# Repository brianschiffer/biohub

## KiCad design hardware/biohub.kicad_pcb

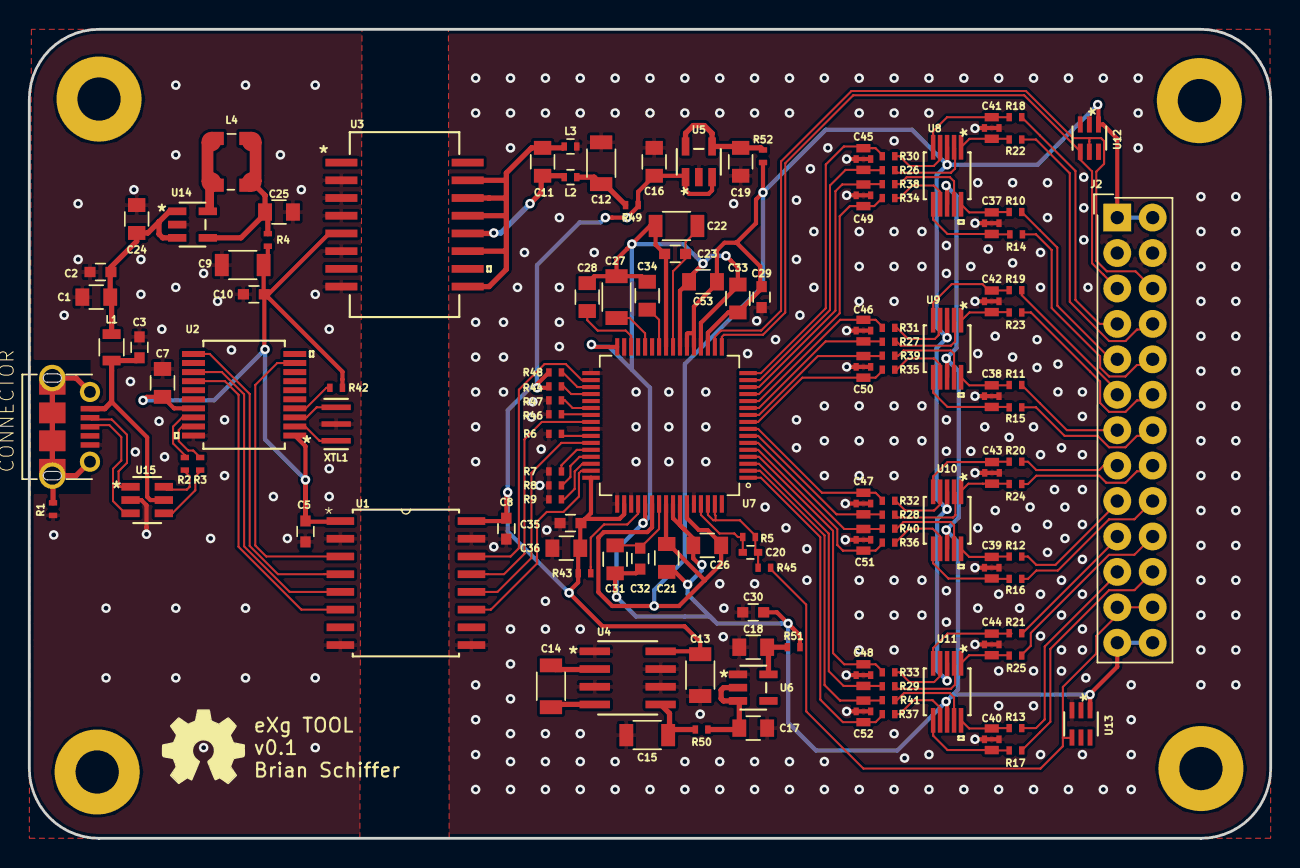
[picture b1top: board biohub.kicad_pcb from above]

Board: 4 copper layers, 89.0 x 58.0 mm, 125 parts (0 on the bottom side), 120 nets.

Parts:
C1, C24, C25: 4.7u; C_0805
C2, C5, C8, C10, C23, C29, C30, C32, C35: 0.1u; C_0603
C3: 10nF; C_0603
C7, C11: 0.22u; C_0805
C9, C12, C13, C14, C15, C22: 10u; C_1206
C16, C17, C18, C19: 2.2u; C_0805
C20: 1n; C_0402
C21, C26, C28, C31, C33, C34, C36, C53: 1u; C_0805
C27: 100u; C_1206
C37, C38, C39, C40, C41, C42, C43, C44: X2Y 10n; 500X14W103MV4T
C45, C46, C47, C48, C49, C50, C51, C52: X2Y 0.22u; 160X14X224MV4T
J1: CONNECTOR; MOLEX_1050170001
J2: Conn_02x13_Odd_Even; MOLEX_70247_2652_2x13
L1: 600R/2A; L_0805
L2, L3: 2.2R/0.2A; L_0402
L4: 4.7uH; L_Wuerth_WE-TPC
R1, R6, R7, R8, R9, R42, R43, R44, R46, R47, R48: 10k; R_0402_NoSilk
R2, R3: 27; R_0402_NoSilk
R4, R49, R50, R51, R52: 0; R_0402_NoSilk
R5, R45: 1M; R_0402_NoSilk
R10, R11, R12, R13, R14, R15, R16, R17, R18, R19, R20, R21, R22, R23, R24, R25: 4.02k 0.1%; R_0402_NoSilk
R26, R27, R28, R29, R30, R31, R32, R33, R34, R35, R36, R37, R38, R39, R40, R41: 10k 0.1%; R_0402_NoSilk
U1: ADUM1412BRWZ
U2: MCP2210-I_SS; MCP2210
U3: ADUM6020
U4: ADM8660ARZ
U5: ADP7142AUJZ-2.5-R7; ADP7142AUJZ-R7
U6: ADP7182AUJZ-2.5-R7; ADP7182AUJZ-R7
U7: ADS1299IPAG
U8, U9, U10, U11: AD8244BRMZ
U12, U13: TPD4E1B06DCKR
U14: MCP1603T-330I
U15: USBLC6-2SC6; USBLC62
XTL1: CSTNE12M0GH5L000R0

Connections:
+2V5: C21.2, C26.2, C29.2, C33.2, C53.2, J2.1, J2.2, R52.2, U7.19, U7.21, U7.22, U7.54, U7.56, U7.59, U8.3, U9.3, U10.3, U11.3, U12.1
+3V3: C8.1, C13.1, C16.1, C35.2, C36.2, R43.1, R44.1, R48.1, R49.2, U1.16, U4.8, U5.1, U5.3, U7.48, U7.50
-2V5: C21.1, C22.1, C23.1, C26.1, C27.1, C28.1, C30.1, C31.1, C32.1, C33.1, C34.1, C53.1, J2.25, J2.26, R51.2, U7.20, U7.23, U7.25, U7.32, U7.53, U7.57, U7.58, U8.8, U9.8, U10.8, U11.8, U13.1
-3V3: C17.1, R50.2, U6.2, U6.3
/AFE/BIAS: J2.23, J2.24, R45.1, U13.4
/AFE/DRDY: U1.11, U7.47
/AFE/MISO: U1.12, U7.43
/AFE/MOSI: U1.14, U7.34
/AFE/SCLK: U1.13, U7.40
/AFE/SRB1: J2.5, U7.17, U12.4
/AFE/SRB2: J2.6, U7.18, U12.5
/interface/1N: C45.1, R26.1, U7.15
/interface/1P: C45.2, R30.1, U7.16
/interface/2N: C49.1, R34.1, U7.13
/interface/2P: C49.2, R38.1, U7.14
/interface/3N: C46.1, R27.1, U7.11
/interface/3P: C46.2, R31.1, U7.12
/interface/4N: C50.1, R35.1, U7.9
/interface/4P: C50.2, R39.1, U7.10
/interface/5N: C47.1, R28.1, U7.7
/interface/5P: C47.2, R32.1, U7.8
/interface/6N: C51.1, R36.1, U7.5
/interface/6P: C51.2, R40.1, U7.6
/interface/7N: C48.1, R29.1, U7.3
/interface/7P: C48.2, R33.1, U7.4
/interface/8N: C52.1, R37.1, U7.1
/interface/8P: C52.2, R41.1, U7.2
/interface/CONN_1N: J2.8, R22.2
/interface/CONN_1P: J2.7, R18.2
/interface/CONN_2N: J2.10, R14.2
/interface/CONN_2P: J2.9, R10.2
/interface/CONN_3N: J2.12, R23.2
/interface/CONN_3P: J2.11, R19.2
/interface/CONN_4N: J2.14, R15.2
/interface/CONN_4P: J2.13, R11.2
/interface/CONN_5N: J2.16, R24.2
/interface/CONN_5P: J2.15, R20.2
/interface/CONN_6N: J2.18, R16.2
/interface/CONN_6P: J2.17, R12.2
/interface/CONN_7N: J2.20, R25.2
/interface/CONN_7P: J2.19, R21.2
/interface/CONN_8N: J2.22, R17.2
/interface/CONN_8P: J2.21, R13.2
/power/2_5_OUT: C19.1, R52.1, U5.4, U5.5
/power/CP1: C14.1, U4.2
/power/CP2: C14.2, U4.4
/power/INV_OUT: C15.1, R50.1, U4.5
/power/n2_5_OUT: C18.1, R51.1, U6.5
/usb/ESD_D+: R3.2, U15.4
/usb/ESD_D-: R2.2, U15.6
/usb/ISO: C11.2, L3.1, U3.9, U3.11, U3.13, U3.14, U3.15
/usb/ISO_VDD_1: C11.1, L2.1, U3.12
/usb/ISO_VDD_2: C12.1, L2.2, R49.1
/usb/LX: L4.1, U14.5
/usb/MCP_D+: R3.1, U2.19
/usb/MCP_D-: R2.1, U2.18
/usb/SHLD: J1.SH1, J1.SH2, J1.SH3, J1.SH4, J1.SH5, J1.SH6, J1.SH7, J1.SH8, R1.1
/usb/USB_D+: J1.3, U15.3
/usb/USB_D-: J1.2, U15.1
/usb/USB_SPI_CLK: U1.4, U2.11
/usb/USB_SPI_DATA_READY: U1.6, U2.14
/usb/USB_SPI_MISO: U1.5, U2.13
/usb/USB_SPI_MOSI: U1.3, U2.9
/usb/VUSB: C3.1, J1.1, L1.2, U15.5
/usb/Vfb: C25.1, L4.2, R4.1, U14.4
GND: C8.2, C12.2, C13.2, C15.2, C16.2, C17.2, C18.2, C19.2, C29.1, C30.2, C35.1, C36.1, C37.3, C37.4, C38.3, C38.4, C39.3, C39.4, C40.3, C40.4, C41.3, C41.4, C42.3, C42.4, C43.3, C43.4, C44.3, C44.4, C45.3, C45.4, C46.3, C46.4, C47.3, C47.4, C48.3, C48.4, C49.3, C49.4, C50.3, C50.4, C51.3, C51.4, C52.3, C52.4, J2.3, J2.4, L3.2, R6.1, R7.1, R8.1, R9.1, R46.1, R47.1, U1.9, U1.15, U4.1, U4.3, U4.6, U4.7, U5.2, U6.1, U7.31, U7.33, U7.41, U7.49, U7.51, U7.60, U12.3, U13.3
GNDD: C1.2, C2.2, C3.2, C5.2, C7.2, C9.2, C10.2, C24.2, C25.2, J1.5, R1.2, U1.2, U1.8, U2.20, U3.2, U3.3, U3.4, U3.6, U3.8, U14.2, U15.2, XTL1.2
unnamed: C20.1, R5.1, R45.2, U7.62, U7.63
unnamed: C20.2, R5.2, U7.61
unnamed: C22.2, C23.2, U7.24
unnamed: C27.2, U7.28
unnamed: C28.2, U7.30
unnamed: C31.2, C32.2, U7.55
unnamed: C34.2, U7.26
unnamed: C37.1, R10.1, U8.10
unnamed: C37.2, R14.1, U8.6
unnamed: C38.1, R11.1, U9.10
unnamed: C38.2, R15.1, U9.6
unnamed: C39.1, R12.1, U10.10
unnamed: C39.2, R16.1, U10.6
unnamed: C40.1, R13.1, U11.10
unnamed: C40.2, R17.1, U11.6
unnamed: C41.1, R18.1, U8.5
unnamed: C41.2, R22.1, U8.1
unnamed: C42.1, R19.1, U9.5
unnamed: C42.2, R23.1, U9.1
unnamed: C43.1, R20.1, U10.5
unnamed: C43.2, R24.1, U10.1
unnamed: C44.1, R21.1, U11.5
unnamed: C44.2, R25.1, U11.1
unnamed: R6.2, U7.42
unnamed: R7.2, U7.44
unnamed: R8.2, U7.45
unnamed: R9.2, U7.46
unnamed: R26.2, U8.2
unnamed: R27.2, U9.2
unnamed: R28.2, U10.2
unnamed: R29.2, U11.2
unnamed: R30.2, U8.4
unnamed: R31.2, U9.4
unnamed: R32.2, U10.4
unnamed: R33.2, U11.4
unnamed: R34.2, U8.7
unnamed: R35.2, U9.7
unnamed: R36.2, U10.7
unnamed: R37.2, U11.7
unnamed: R38.2, U8.9
unnamed: R39.2, U9.9
unnamed: R40.2, U10.9
unnamed: R41.2, U11.9
unnamed: R42.1, U2.4
unnamed: R43.2, U7.52
unnamed: R44.2, U7.36
unnamed: R46.2, U7.39
unnamed: R47.2, U7.38
unnamed: R48.2, U7.35
unnamed: U2.2, XTL1.1
unnamed: U2.3, XTL1.3
VBUS: C1.1, C2.1, C24.1, L1.1, U14.1, U14.3
VCOM: C5.1, C7.1, C9.1, C10.1, R4.2, R42.2, U1.1, U2.1, U2.17, U3.5

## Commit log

2018-11-08 Initial commit
    Partially started schematics & symbols
2018-11-09 Added Buffers/ESD Protection
2018-11-10 Updated to heirarchy sheets
    Also added more ESD protection
2018-11-10 Update hierarchy sheets
2018-11-11 Started BOM & Switched to X2Y Caps
2018-11-11 Part swaps & BOM completion
2018-11-11 Finished assigning footprints
2018-11-11 Rough part placement
2018-11-11 Placement cleanup
2018-11-12 Near final placement
2018-11-12 Added Copper Pours
2018-11-13 Added 3.3V buck & started layout
2018-11-13 Updated step model
2018-11-14 Started layout
2018-11-15 First full layout
2018-11-16 Added USB ESD Protection
2018-11-17 Expanded outline to fix mounting hole interference
2018-11-17 Updated solder mask & paste clearance
2024-01-23 New SW GUI

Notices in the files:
parts and their libraries:
Copyright 2016 Accelerated Designs. All rights reserved.
